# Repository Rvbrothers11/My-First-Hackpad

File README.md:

# My-First-Hackpad
My first hackpad insipred from https://blueprint.hackclub.com/hackpad

Bill of Materials:
sk6812 mini-e leds (x4): $1 Total
Cherry MX switches (x4): $7 Total
Seeed XIAO RP2040 (x1): $4.65
MX switches Keycaps (x4): $1.2 Total
EC11 Rotary Encoders (x2): $1.9 Total
Rotary Encoder Cap (x2): $1.33 Total
Total: $17.08

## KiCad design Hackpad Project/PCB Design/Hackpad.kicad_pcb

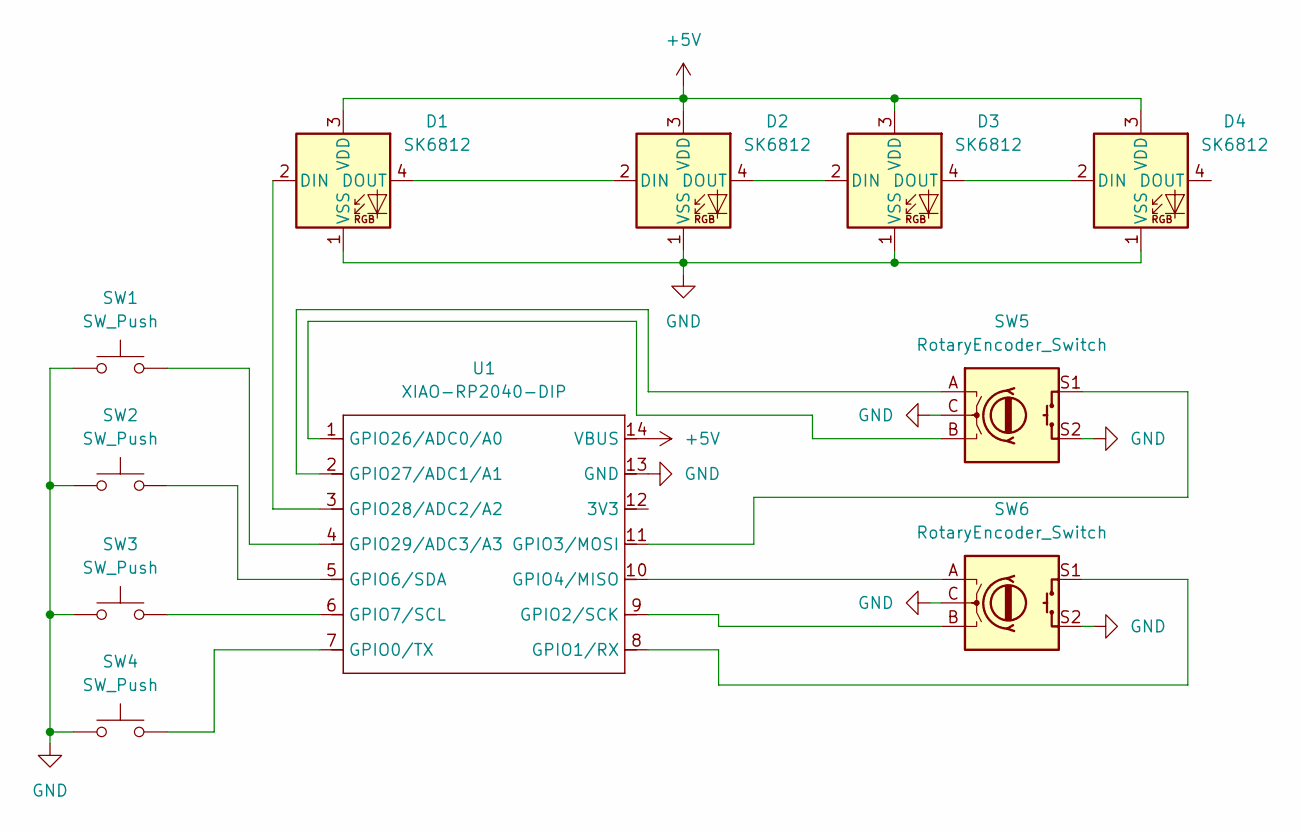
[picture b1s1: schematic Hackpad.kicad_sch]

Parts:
D1, D2, D3, D4: SK6812; LED_SK6812MINI_PLCC4_3.5x3.5mm_P1.75mm
SW1, SW2, SW3, SW4: SW_Push; SW_Cherry_MX_1.00u_PCB
SW5, SW6: RotaryEncoder_Switch; RotaryEncoder_Alps_EC11E-Switch_Vertical_H20mm
U1: XIAO-RP2040-DIP

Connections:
+5V: D1.3 (VDD), D2.3 (VDD), D3.3 (VDD), D4.3 (VDD), U1.14 (VBUS)
GND: D1.1 (VSS), D2.1 (VSS), D3.1 (VSS), D4.1 (VSS), SW1.1, SW2.1, SW3.1, SW4.1, SW5.C, SW5.S2, SW6.C, SW6.S2, U1.13 (GND)
unnamed: D1.2 (DIN), U1.3 (GPIO28/ADC2/A2)
unnamed: D1.4 (DOUT), D2.2 (DIN)
unnamed: D2.4 (DOUT), D3.2 (DIN)
unnamed: D3.4 (DOUT), D4.2 (DIN)
unnamed: SW4.2, U1.7 (GPIO0/TX)
unnamed: SW6.S1, U1.8 (GPIO1/RX)
unnamed: SW6.B, U1.9 (GPIO2/SCK)
unnamed: SW5.S1, U1.11 (GPIO3/MOSI)
unnamed: SW6.A, U1.10 (GPIO4/MISO)
unnamed: SW2.2, U1.5 (GPIO6/SDA)
unnamed: SW3.2, U1.6 (GPIO7/SCL)
unnamed: SW5.B, U1.1 (GPIO26/ADC0/A0)
unnamed: SW5.A, U1.2 (GPIO27/ADC1/A1)
unnamed: SW1.2, U1.4 (GPIO29/ADC3/A3)

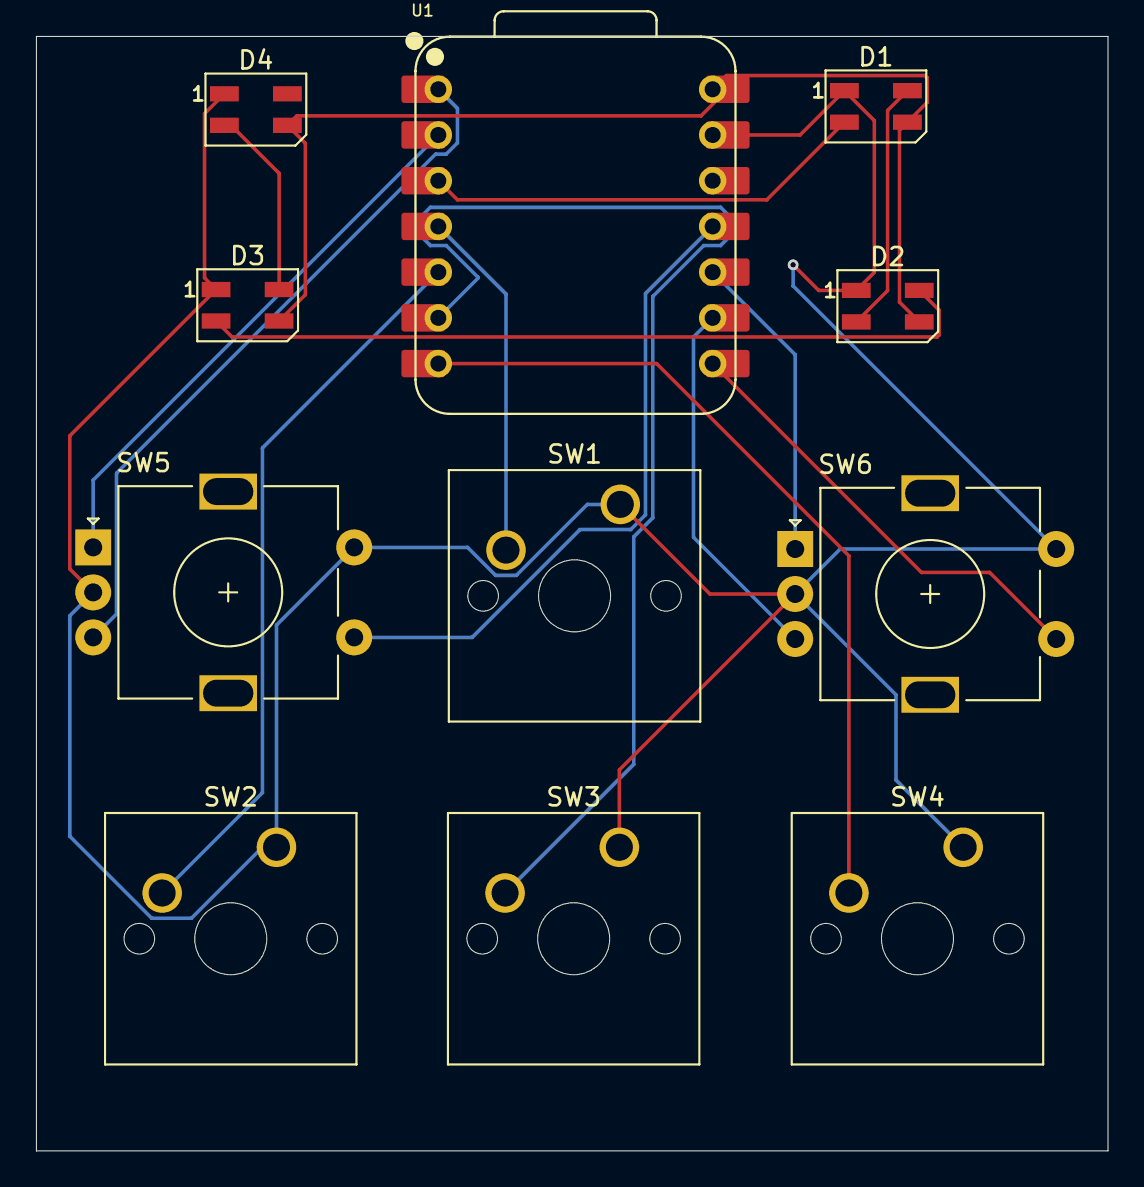
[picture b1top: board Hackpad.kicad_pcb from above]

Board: 2 copper layers, 59.5 x 61.9 mm, 11 parts (0 on the bottom side), 16 nets.

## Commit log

2026-01-15 README.md
